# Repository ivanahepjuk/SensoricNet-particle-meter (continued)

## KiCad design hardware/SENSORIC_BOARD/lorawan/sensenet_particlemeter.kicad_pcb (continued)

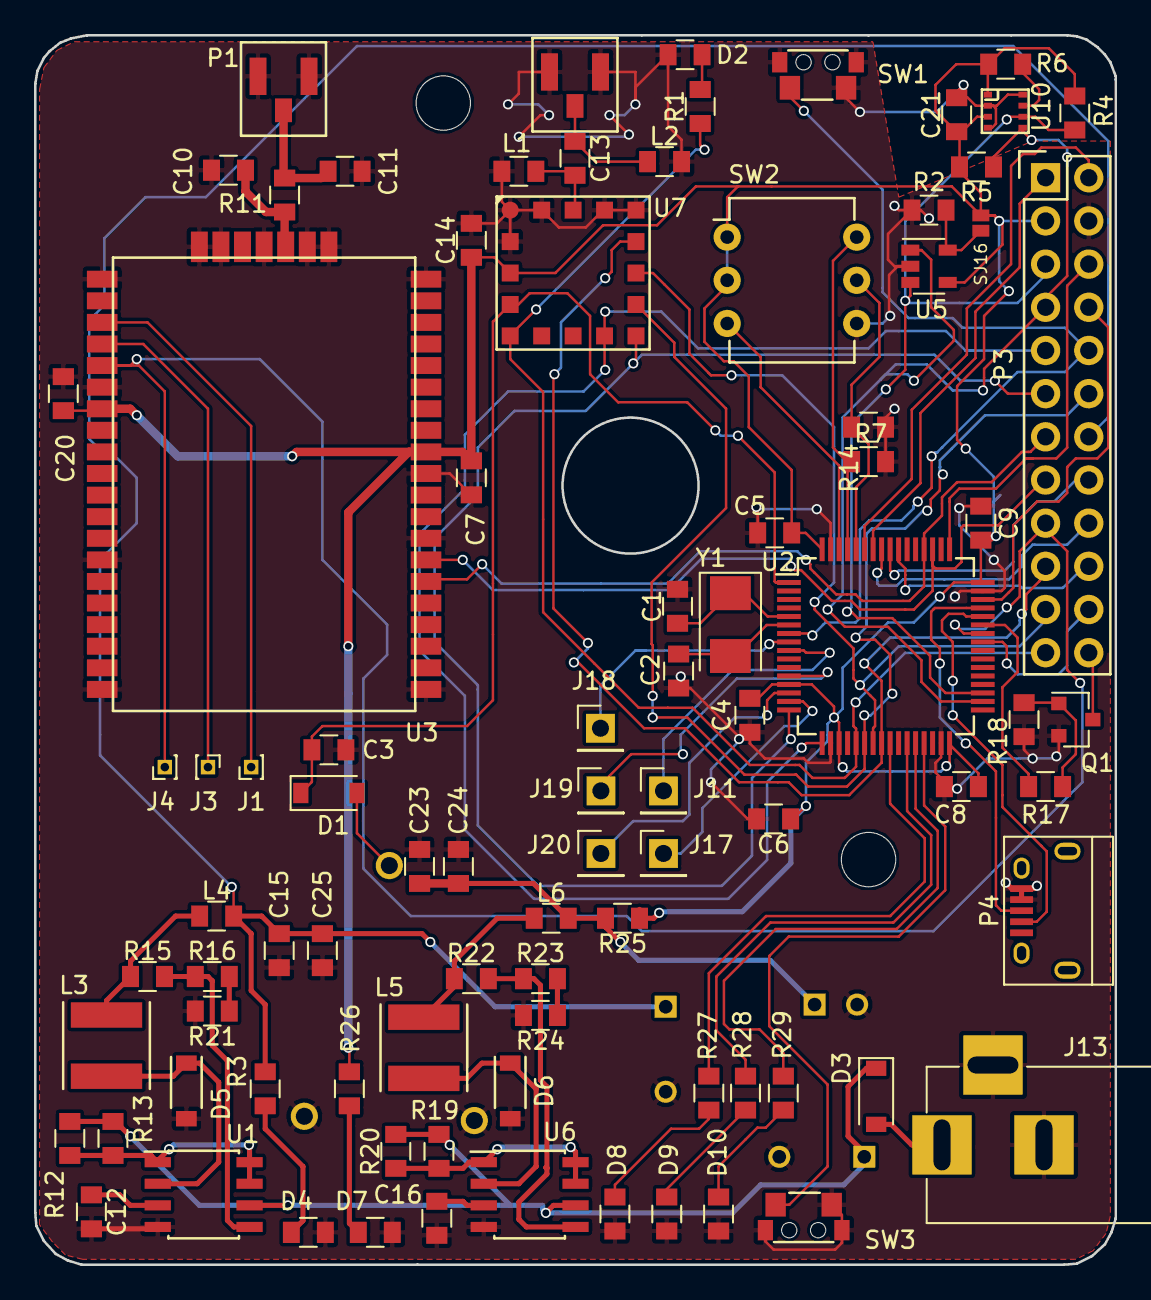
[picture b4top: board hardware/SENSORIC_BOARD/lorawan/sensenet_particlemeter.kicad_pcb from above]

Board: 2 copper layers, 63.6 x 72.3 mm, 95 parts (0 on the bottom side), 73 nets.

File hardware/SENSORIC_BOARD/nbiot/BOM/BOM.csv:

"Id";"Designator";"Package";"Quantity";"Designation";"Supplier and ref";
1;"U2";"TQFP-64_10x10mm_Pitch0.5mm";1;"stm32f072";;;
2;"BT1";"BAT-CR2032_bottom";1;"Battery_Cell";;;
3;"C3,C6,C9,C13,C4,C8";"SMD_0805";6;"C";;;
4;"C5,C7,C21,C25";"SMD_0805";4;"100n";;;
5;"C10,C11";"SMD_0805";2;"NC";;;
6;"C14";"SMD_0805";1;"2,2u";;;
7;"C23";"SMD_0805";1;"10u";;;
8;"C24";"SMD_0805";1;"220n";;;
9;"D1";"D_SOD-123";1;"D_Schottky";;;
10;"D2,D4,D7,D8,D9,D10";"SMD_0805";6;"LED";;;
11;"D3";"D_SOD-123";1;"D_Schottky_ss14";;;
12;"J1,J2,J3,J4,J21";"Pin_Header_Straight_1x01_Pitch1.00mm";5;"CONN_01X01";;;
13;"J5,J6";"MountingHole_3.2mm_M3_DIN965";2;"CONN_01X01";;;
14;"J13";"BARREL_JACK";1;"BARREL_JACK";;;
15;"L2,L1";"SMD_0805";2;"L";;;
16;"P1,P2";"Antenna_conn";2;"SMA_mini";;;
17;"R1,R17,R18,R27,R28,R29";"SMD_0805";6;"R";;;
18;"R2,R4,R5";"SMD_0805";3;"4.7k";;;
19;"R3,R26";"SMD_0805";2;"5k6";;;
20;"R6";"SMD_0805";1;"22k";;;
21;"R7,R10,R14";"SMD_0805";3;"10k";;;
22;"R8,R9";"SMD_0805";2;"1k";;;
23;"U3";"quectel_BC95";1;"QUECTEL_BC95";;;
24;"U7";"M10578";1;"M10578-A2";;;
25;"U10";"BME280";1;"bme280_barebone";;;
26;"J11,J17,J18,J19,J20";"Pin_Header_Straight_1x01_Pitch2.54mm";5;"CONN_01X01";;;
27;"SJ16";"solder_jumper";1;"solder_jumper";;;
28;"Y1";"Crystal_SMD_5032-2pin_5.0x3.2mm";1;"8MHz";;;
29;"C1,C2";"SMD_0805";2;"4.3p";;;
30;"C12";"SMD_0805";1;"510pF";;;
31;"C15";"SMD_0805";1;"1u";;;
32;"R12,R19";"SMD_0805";2;"0R33";;;
33;"R13,R20,R21,R24";"SMD_0805";4;"tbd";;;
34;"R15";"SMD_0805";1;"27k";;;
35;"R16";"SMD_0805";1;"9.1k";;;
36;"U1,U6";"SOIC-8_3.9x4.9mm_Pitch1.27mm";2;"MC33063";;;
37;"U5";"SOT-23-5";1;"CAT24C02";;;
38;"Q1";"SOT-23";1;"Q_NMOS_GSD";;;
39;"U4";"nanosimmm";1;"SIM";;;
40;"R11";"SMD_0805";1;"0R";;;
41;"C16";"SMD_0805";1;"352pF";;;
42;"R22";"SMD_0805";1;"18k";;;
43;"R23";"SMD_0805";1;"11k";;;
44;"R25,R30";"SMD_0805";2;"0R1";;;
45;"L3";"Inductor_Taiyo-Yuden_NR-50xx";1;"39uH";;;
46;"L5";"Inductor_Taiyo-Yuden_NR-50xx";1;"41uH";;;
47;"D5,D6";"SOD-123";2;"1N5819";;;
48;"C17,C19";"C_Radial_D10_L16_P5_bottom";2;"1000u";;;
49;"C18";"C_Radial_D6.3_L11.2_P2.5_bottom";1;"470uF";;;
50;"P3";"Pin_Header_Straight_2x12";1;"CONN_02X12";;;
51;"SW2";"DIP-6_W7.62mm";1;"SW_DIP_x03";;;
52;"SW1,SW3";"edge_switch";2;"SW_DPST";;;
53;"U8";"USB_Micro-B";1;"usb_femalee";;;
54;"L4,L6";"SMD_0805";2;"1uH";;;
55;"";"drawing";1;"";;;

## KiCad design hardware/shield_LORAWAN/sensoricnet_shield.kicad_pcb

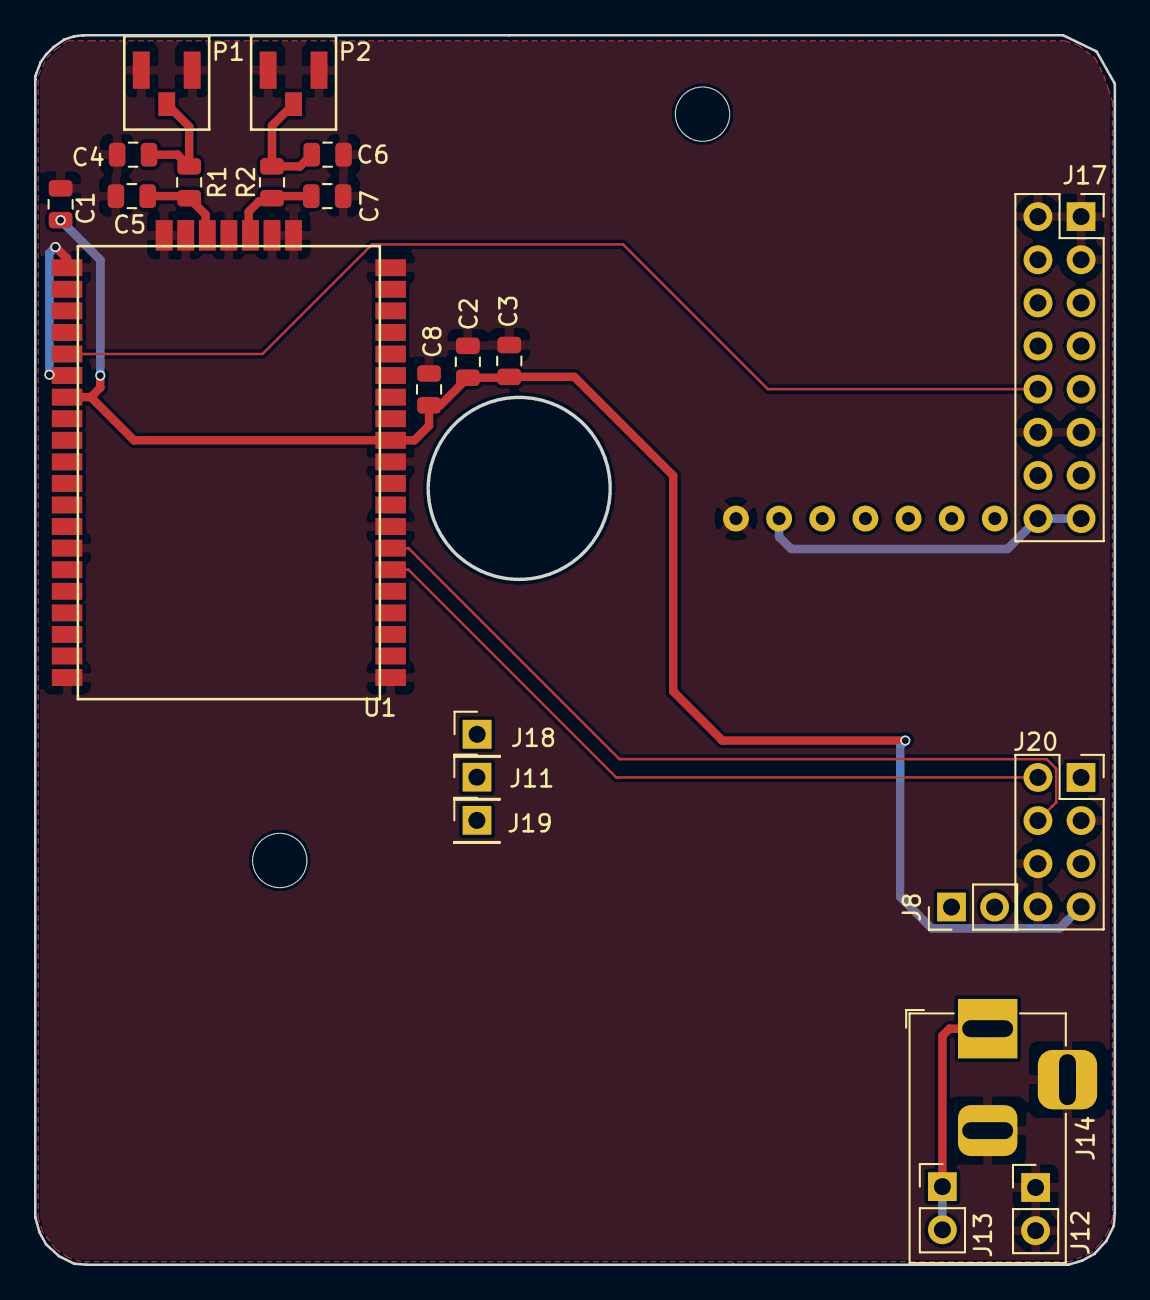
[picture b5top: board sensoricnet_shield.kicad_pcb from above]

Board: 2 copper layers, 63.6 x 72.4 mm, 27 parts (0 on the bottom side), 11 nets.

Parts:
C1, C8: 100n; C_0805_2012Metric
C2: 1u; C_0805_2012Metric
C3: 22p; C_0805_2012Metric
C4, C5, C6, C7: DNP; C_0805_2012Metric
J5, J6: CONN_01X01; MountingHole_3.2mm_M3_DIN965
J7: Conn_01x07_Female; OLED
J8: Conn_02x01; PinHeader_1x02_P2.54mm_Vertical
J11, J18, J19: CONN_01X01; PinHeader_1x01_P2.54mm_Vertical
J12: Barrel_Jack_Switch; BarrelJack_Horizontal
J13, J14: Conn_01x02_Female; PinHeader_1x02_P2.54mm_Vertical
J17: Conn_02x08_Odd_Even; PinSocket_2x08_P2.54mm_Vertical
J20: Conn_02x04_Odd_Even; PinSocket_2x04_P2.54mm_Vertical
LOGO1: LOGO; PCB_artwork
LOGO2: LOGO; OSHW-Logo2_9.8x8mm_BackSilkScreen
P1, P2: SMA_mini; Antenna_conn
R1, R2: 0R; R_0805_2012Metric
U1: RN2483; RN2483_top

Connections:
+3V3: C1.1, C2.1, C3.1, C8.2, J20.7, U1.12, U1.34
+5V: J7.2, J17.15, J17.16
+9V: J12.1, J13.1, J13.2
GND: C1.2, C2.2, C3.2, C4.1, C5.1, C6.1, C7.1, C8.1, J7.1, J12.2, J12.3, J14.1, J14.2, J17.1, J17.2, J17.3, J17.11, J17.12, J20.3, J20.6, J20.8, P1.1, P1.3, P2.1, P2.3, U1.1, U1.8, U1.11, U1.20, U1.21, U1.22, U1.24, U1.26, U1.27, U1.28, U1.33, U1.41, U1.47
unnamed: C4.2, P1.2, R1.1
unnamed: C5.2, R1.2, U1.25
unnamed: C6.2, P2.2, R2.1
unnamed: C7.2, R2.2, U1.23
Rx: J20.2, U1.6
Tx: J20.4, U1.7
WIRELESS_reset: J17.10, U1.32

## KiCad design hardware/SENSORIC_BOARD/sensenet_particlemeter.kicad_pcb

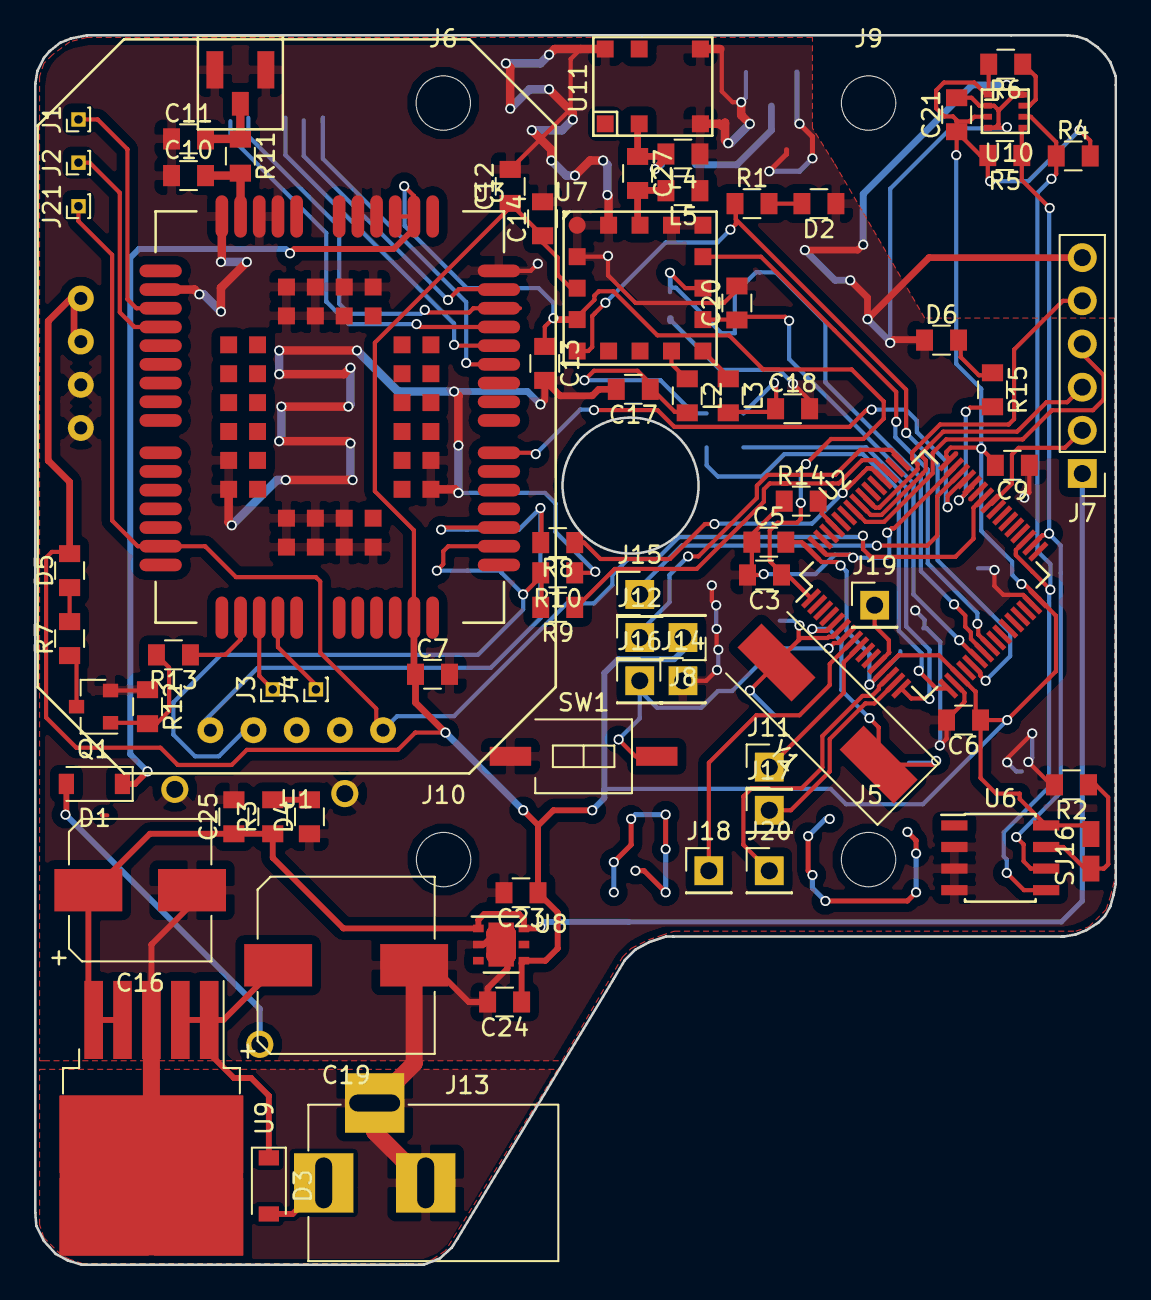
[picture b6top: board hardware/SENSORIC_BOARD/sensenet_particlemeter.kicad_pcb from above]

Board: 2 copper layers, 63.6 x 72.3 mm, 91 parts (0 on the bottom side), 64 nets.

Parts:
BT1: Battery_Cell; BAT-CR2032_bottom
C1, C2: 4.3p; SMD_0805_bottom
C3, C6, C9, C27: C; SMD_0805
C4, C8: C; SMD_0805_bottom
C5, C7, C21: 100n; SMD_0805
C10, C11: NC; SMD_0805
C12, C13, C17, C18, C20: 22p; SMD_0805
C14: 2,2u; SMD_0805
C16: 220n; CP_Elec_8x10
C19: 470u; CP_Elec_10x10
C22: 22p; SMD_0805_bottom
C23, C25: 10u; SMD_0805
C24: 220n; SMD_0805
D1: D_Schottky; D_SOD-123
D2, D4, D5, D6: LED; SMD_0805
D3: D_Schottky_ss14; D_SOD-123
J1, J2, J3, J4, J21: CONN_01X01; Pin_Header_Straight_1x01_Pitch1.00mm
J5, J6, J9, J10: CONN_01X01; MountingHole_3.2mm_M3_DIN965
J7: CONN_01X06; Pin_Header_Straight_1x06_Pitch2.54mm
J8, J11, J12, J14, J15, J16, J17, J18, J19, J20: CONN_01X01; Pin_Header_Straight_1x01_Pitch2.54mm
J13: BARREL_JACK
L2, L3: 47n; SMD_0805
L4, L5: L; SMD_0805
P1: SMA_mini; Antenna_conn
P2: SMA_mini; Antenna_conn_bott
Q1: Q_NPN_BCV71; SOT-23
R1: R; SMD_0805
R2, R4, R5, R13: 4.7k; SMD_0805
R3: 5k6; SMD_0805
R6: 22k; SMD_0805
R7, R8, R9, R15: 1k; SMD_0805
R10, R14: 10k; SMD_0805
R11: 0R; SMD_0805
R12: 47k; SMD_0805
SJ1, SJ15, SJ17: solder_jumper; solder_jumper_bott
SJ16: solder_jumper
SW1: SW_Push; SW_DIP_x1_W8.61mm_Slide_SMD_LowProfile
U1: wireless_patice; wireless_footprint
U2: stm32f072; TQFP-64_10x10mm_Pitch0.5mm
U3: QUECTEL_BC95; quectel_BC95
U4: SIM; nanosim_bottom
U6: M24C04; SOIC-8_3.9x4.9mm_Pitch1.27mm
U7: M10578-A2; M10578
U8: LD39050; DFN-6-1EP_3x3mm_Pitch0.95mm
U9: NCP59150; TO-263-5_TabPin3
U10: bme280_barebone; BME280
U11: SR4G008
Y1: 8MHz; Crystal_SMD_HC49-SD

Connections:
+3V3: C4.1, C5.2, C6.1, C7.1, C8.1, C9.2, C12.1, C14.1, C21.1, C23.1, C24.1, D5.2, J8.1, R4.2, R5.2, R6.2, SJ16.2, U1.1, U1.2, U2.13, U2.19, U2.32, U2.48, U2.64, U3.26, U6.8, U7.15, U8.4, U10.1, U10.3
+5V: C16.1, C25.1, J7.1, R3.1, U8.1, U8.6, U9.4, U9.5
GND: BT1.2, BT1.3, C1.2, C2.2, C3.2, C4.2, C5.1, C6.2, C7.2, C8.2, C9.1, C10.1, C11.1, C12.2, C13.2, C14.2, C16.2, C17.2, C18.2, C19.2, C20.2, C21.2, C22.2, C23.2, C24.2, C25.2, D2.1, D4.1, D6.1, J7.6, J13.2, J13.3, J14.1, L4.1, L5.1, P1.1, P1.3, P2.1, P2.3, Q1.2, R2.2, R10.1, R12.1, R14.1, SW1.1, U1.3, U1.4, U2.18, U2.31, U2.47, U2.63, U3.2, U3.43, U3.47, U3.48, U3.51, U3.52, U3.54, U3.59, U3.60, U3.61, U3.62, U3.63, U3.64, U3.65, U3.66, U3.71, U3.72, U3.73, U3.74, U3.81, U3.82, U3.83, U3.92, U3.93, U3.94, U6.2, U6.3, U6.4, U7.1, U7.2, U7.4, U7.5, U7.16, U8.2, U8.7, U9.3, U10.2, U10.4, U10.8, U11.3, U11.4, U11.6
unnamed: BT1.1, D1.2
unnamed: C1.1, U2.5, Y1.1
unnamed: C2.1, U2.6, Y1.2
unnamed: C10.2, R11.2, U3.53
unnamed: C11.2, P1.2, R11.1
unnamed: C17.1, L2.2, SJ15.2
unnamed: C18.1, L3.2, SJ17.2
unnamed: C19.1, D3.1, U9.1, U9.2
unnamed: C27.1, L4.2, SJ1.1, U11.2
unnamed: D2.2, R1.2
unnamed: D3.2, J13.1
unnamed: D4.2, R3.2
unnamed: D5.1, R7.2
unnamed: D6.2, R15.1
unnamed: J1.1, U3.3
unnamed: J2.1, U3.4
unnamed: J3.1, U3.19
unnamed: J4.1, U3.20
unnamed: J11.1, U2.9
unnamed: J17.1, U2.15
unnamed: J18.1, U2.8
unnamed: J19.1, U2.12
unnamed: J20.1, U2.14
unnamed: L2.1, U7.10
unnamed: L3.1, U7.9
unnamed: P2.2, SJ1.2
unnamed: Q1.1, R12.2, R13.2
unnamed: Q1.3, R7.1
unnamed: R2.1, SJ16.1, U6.7
unnamed: R6.1, U10.7
unnamed: R8.2, U1.5, U3.30
unnamed: R9.2, R10.2, U1.6, U3.29
unnamed: R13.1, U3.18
unnamed: R14.2, U2.60
unnamed: R15.2, U2.44
unnamed: U3.38, U4.6
unnamed: U3.39, U4.4
unnamed: U3.40, U4.1
unnamed: U3.41, U4.2
unnamed: U3.42, U4.5
PM_SCK: J7.5, U2.55
PM_SDI: J7.4, U2.57
PM_SDO: J7.3, U2.56
PM_SS: J7.2, U2.41
RI: U2.45, U3.34
Rx: R8.1, U2.52
SWD_CLK: J12.1, U2.49
SWD_DIO: J15.1, U2.46
Tx: R9.1, U2.51
UART_GPS_RX: SJ15.1, U2.17
UART_GPS_TX: SJ17.1, U2.16
WIRELESS_reset: J21.1, U1.9, U2.42, U3.15
antenna: C27.2, L5.2, U7.3
batt: C3.1, C13.1, D1.1, U2.1, U3.45, U3.46, U7.14
gps_fix: R1.1, U2.21, U7.13
gps_pulses: U2.24, U7.6
gps_reset: C22.1, U2.23, U7.7
gps_standby: C20.1, U2.22, U7.8
i2c_scl: R5.1, U2.34, U6.6, U10.5
i2c_sda: R4.1, U2.35, U6.5, U10.6
reset: J16.1, SW1.2, U2.7

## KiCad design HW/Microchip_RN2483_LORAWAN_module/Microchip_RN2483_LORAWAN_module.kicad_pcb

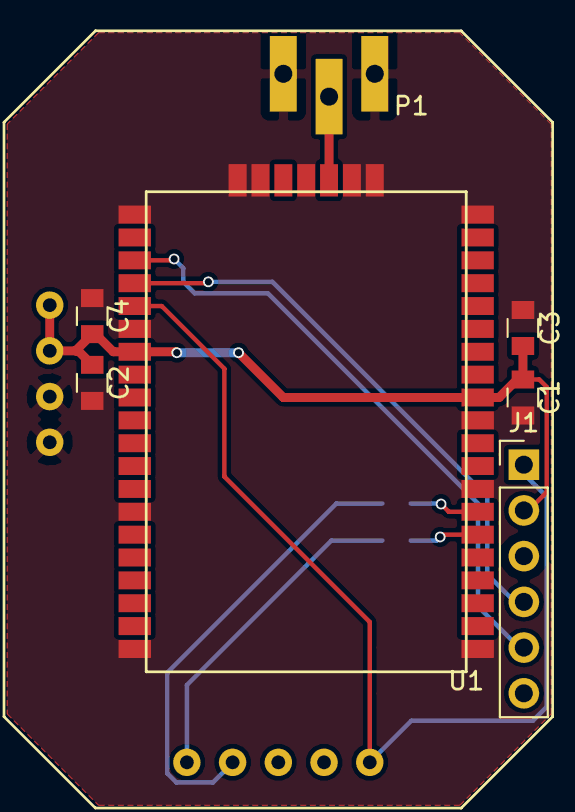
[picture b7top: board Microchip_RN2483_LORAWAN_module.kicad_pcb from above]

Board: 2 copper layers, 10 parts (0 on the bottom side), 10 nets.

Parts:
C1, C4: 100n; SMD_0805
C2, C3: 56p; SMD_0805
J1: Conn_01x06; Pin_Header_Straight_1x06_Pitch2.54mm
P1: SMA_mini; sma_conn
SJ1, SJ2: solder_jumper; solder_jumper_bott
U1: RN2483; RN2483_top
U2: wireless_patice; wireless_footprint

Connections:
+3V3: C1.1, C2.1, C3.2, C4.2, J1.2, U1.12, U1.34, U2.1, U2.2
GND: C1.2, C2.2, C3.1, C4.1, J1.3, P1.1, P1.3, U1.1, U1.8, U1.11, U1.20, U1.21, U1.22, U1.24, U1.26, U1.27, U1.28, U1.33, U1.41, U1.47, U2.3, U2.4
unnamed: J1.4, U1.31
unnamed: J1.5, U1.30
unnamed: P1.2, U1.23
unnamed: SJ1.1, U1.7
unnamed: SJ1.2, U2.6
unnamed: SJ2.1, U1.6
unnamed: SJ2.2, U2.5
rn2483_reset: J1.1, U1.32, U2.9

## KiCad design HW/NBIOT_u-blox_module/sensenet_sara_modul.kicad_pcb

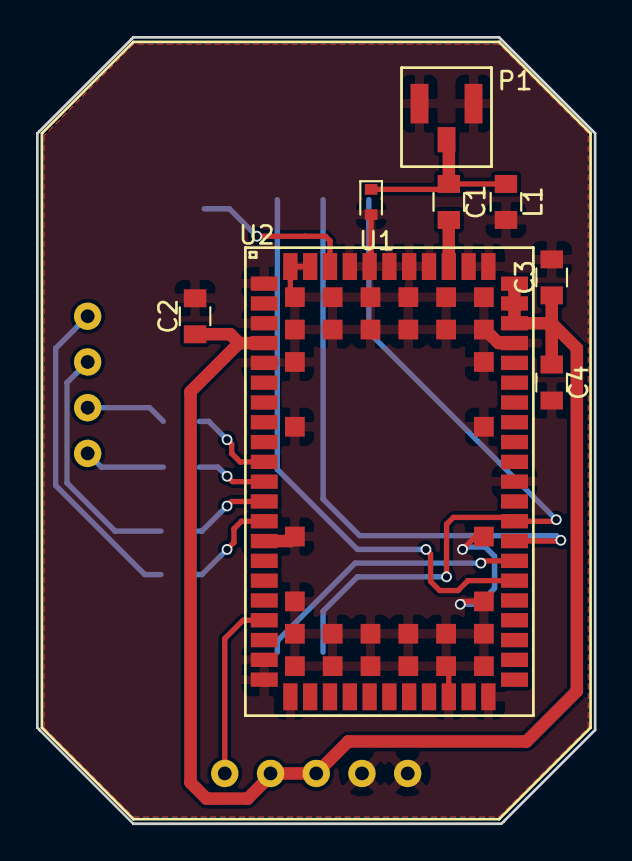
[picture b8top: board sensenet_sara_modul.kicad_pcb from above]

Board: 2 copper layers, 31.0 x 43.7 mm, 15 parts (0 on the bottom side), 18 nets.

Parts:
ANTENNA_DET1: ANTENNA_DET; smd_point_bottom
C1: 4.3pF; C_0805
C2, C4: 100n; C_0805
C3: 56p; C_0805
L1: L; C_0805
P1: SMA_mini; Antenna_conn
SJ1, SJ2, SJ3, SJ4: solder_jumper; solder_jumper_bott
U1: ESD5B5; D_SOD-523
U2: SARA-N210; SARA
U3: SIM; SIM2
U4: wireless_pcb_modul; wireless_footprint

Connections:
3.3V: C2.1, C3.1, C4.1, U2.4, U2.51, U2.52, U2.53, U4.6, U4.7
GND: C2.2, C3.2, C4.2, L1.2, P1.1, P1.3, U1.2, U2.1, U2.3, U2.5, U2.14, U2.20, U2.21, U2.22, U2.30, U2.32, U2.43, U2.50, U2.54, U2.55, U2.57, U2.58, U2.59, U2.60, U2.61, U2.63, U2.64, U2.65, U2.66, U2.67, U2.68, U2.69, U2.70, U2.71, U2.72, U2.73, U2.74, U2.75, U2.76, U2.77, U2.78, U2.79, U2.80, U2.81, U2.82, U2.83, U2.84, U2.85, U2.86, U2.87, U2.88, U2.89, U2.90, U2.91, U2.92, U2.93, U2.94, U2.95, U2.96, U3.3, U4.8, U4.9
unnamed: ANTENNA_DET1.1, U2.62
unnamed: C1.1, L1.1, P1.2, U1.1
unnamed: C1.2, U2.56
unnamed: SJ1.2, U2.11
unnamed: SJ2.2, U2.13
unnamed: SJ3.2, U2.10
unnamed: SJ4.2, U2.12
unnamed: U2.38, U3.6
unnamed: U2.39, U3.1
unnamed: U2.40, U3.5
unnamed: U2.41, U3.2, U3.4
SARA_reset: U2.18, U4.5
UART_CTS: SJ1.1, U4.4
UART_RTS: SJ3.1, U4.3
UART_RX: SJ2.1, U4.1
UART_TX: SJ4.1, U4.2

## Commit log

2018-01-02 This is the first official commit to the SensoricNet particle meter repository. In the past, there were more repositories and it was a bit chaotic, but from now there will be only one, both for fW an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
2018-01-02 picture added
2018-01-02 libopencm3 submodule tweaking eeej
2018-01-02 cleaning up a bit
2018-01-02 inc folder, src folder, makefile, cleaning
2018-01-02 bflmpsvz
2018-01-18 lorawan accepting commands
2018-01-22 opc-n2 improved booting stability
2018-01-27 a bit lost here
2018-01-29 hoooou hou hou
2018-01-31 mensi progres
2018-02-01 basic setup documentation for fedora
2018-02-05 spi problems
2018-02-05 spi stable, commit before cleaning
2018-02-06 SPI working, compilation errors cleaned, measured data are going out to USART4
2018-02-06 small update
2018-02-07 code refactorization
2018-02-07 folders juggling
2018-02-08 lorawan start
2018-02-14 predmdovolenou, dopiste co chcete, je to na vas..
2018-02-27 pridani cayenne lpp knihovny
2018-02-27 oprava gitignore
2018-03-04 cayennelpp, pokus o semihosting
2018-03-04 rozchozeni semihostingu, pridany debug vypisy
2018-03-04 encoding do hexa
2018-03-04 drobne opravy
2018-03-05 rozdelana prace na cteni dat z rn2483 po seriaku. nefunguje to ale
2018-03-06 pred tim nez to cele rozvrtam abych prisel na to kde je problem s opcn2
2018-03-06 ladime
2018-03-06 aaaa
2018-03-06 debug cteni z usartu, nefunguje to
2018-03-13 nejak se ztratilo readme...
2018-03-16 daily update - nefunguje usart4 receive chars
2018-03-17 z*urveny usart
2018-03-19 usart jede
2018-03-19 meri particles a odesila data
2018-03-21 memory leak asi opraveny
2018-03-21 Nb-IOT i LORAWAN ready na test stability, pridan main.h s konfiguracnima definama, uklizeno v ramci moznosti
2018-04-02 eeprom write dodelat
2018-04-03 Pripraveno na eeprom cteni/zapis ID
2018-04-03 priprava na gps modul
2018-04-04 cteni/psani do eeprom funguje
2018-04-06 AAAAAAAA nesnasim particle meter
2018-04-06 asi to jede a bude potreba vyresit robustnejsi zdroje
2018-04-11 uklid kodu, lora zase funkcni, pridan provisioning z csv souboru
2018-04-12 lora: oprava datarate, prubezne ukladani frame counteru
2018-04-13 pokus dale ucesat kod, ale nejak se mi to ted seka a nemam u sebe debug. tento commit nemergeovat!
2018-04-13 vypada to funkcne, z nejakeho duvodu musim odpojit programator
2018-04-15 pokus o uchozeni mereni relativni vlhkosti. zkontroloval jsem kompenzacni matematiku a nevidim tam problem, relativni vlhkost to uz meri, ale se zapornym znamenkem, coz zjevne neni ok. TODO
2018-04-16 upstream merge
2018-04-16 oprava cteni relativni vhlkosti a uklid v knihovne (volani zacinaji na BME_)
2018-04-18 wtf commit
2018-05-02 daily
2018-05-02 usart 4 na wireless mi funguje preruseni, tzn kdyz do patice od wireless pripojim ftdi externi adapter, tak cokoliv v terminalu napisu, snpm mi vrati zpet.
2018-05-02 interrupt predelany na USART2, ale neotestovany, protoze na vyvojove desce je USART2 pristupny po odpajeni jumperu
2018-05-12 pred gps branch
2018-05-13 gps ladeni, nbiot_connect() je zakomentovana
2018-05-13 download nove libopencm3, uprava makefile - doplneni jineho ld scriptu
2018-05-14 rozdelany histogram
2018-05-26 vikend gps pred
2018-05-26 testcommit
2018-05-26 gps fixuje, interrupt jede
2018-05-27 posila hromady znaku a v preruseni precte data z gps
2018-05-28 nejak se to rozbilo, checkout zpatky
2018-05-29 vytahne z gpsky floaty souradnic
2018-06-08 ani nevim, co sem timto myslel
2018-07-13 nbiot preroutovany
2018-07-13 nbiot preroutovany 2
2018-07-14 Zaklad nove verze je hotovy, ted jdu udelat vetsi zmeny v napajeni a layoutu, priprava na shield atd.
2018-07-14 Novy rozmer desky, zmena napajeni z LDO na step down, pridany 1000uF na 5V
2018-07-17 zonglovani zase s gitem
2018-07-18 objednavam prototypy
2018-07-19 pridana kompilace gps souradnic. workaround nefunkcni gps
2018-07-19 Revert "pridana kompilace gps souradnic. workaround nefunkcni gps"
    This reverts commit 8a733ff54c9069909556b1e6c9c11308b894000c.
2018-07-19 pridana kompilace gps souradnic z csv jako workaround nefunkcni gps
2018-07-30 pred debugem noveho hardwaru
2018-08-04 modifikace led diod v hw verzi 2
2018-08-08 redefinice led, inicializace USART1 pro debug vystupy, debug fce
2018-08-13 cteni z gps funkcni, parsovani priste...
2018-08-14 v get_nth_substring je chyba, ale radeji to commitnu a odladim potom
2018-08-15 neotestovana oprava
2018-08-15 naznak parsingu gps pozice
2018-08-16 dodelano parsovani gps souradnic, bez anteny to bohuzel neoverim
2018-08-18 nadhozeny konvert gps to wgs, todo
2018-08-19 funkce pro konverzi gps na wgs84, je to kompilovatelne, nutne otestovat
2018-08-19 opravy a testovani
2018-08-28 funkcni cteni z gps a odesilani souradnic pres IoT
2018-09-04 blabla
2018-09-05 pokus o opravu prepoctu formatu gps souradnic. Nemam jak otestovat
2018-09-05 rozchazeni
2018-09-05 oprava velikosti gps promennych a doplneni prepoctu E-W a N-S
2018-09-06 pred mergnutim opravy souradnic
2018-09-06 Startovaci bod pro praci na hw 2.0
2018-09-07 pred zonglovanim s githubem
2018-09-07 libopencm3 problems
2018-09-07 snad sem vyhodil libopencm3 z tracked files..?
2018-09-07 Cteni statistik site
2018-09-07 Cteni statistik site 2
2018-09-07 poresene preruseni pri cteni z SPI
2018-09-07 opravene zamrzani kvuli preruseni - tedka je preruseni na gpsce aktivni jen kdyz se ceka na konci smycky
2018-09-19 pred prepnuti do nove vetve
2018-09-24 pred displayem
2018-10-16 novy hw
2018-10-17 oled nejede
2018-10-18 pm divnej
2018-11-20 snazim se rozchodit novou serii, jebne me z toho z chvili
2018-11-21 novy hw FLASHABLE, watchdog resi spoustu problemu:)
2018-11-21 prvni deska trial run, NMOSem spinany pmeter
2018-11-24 watchdog restartuje, posila se statistika site, nektere padaji a nektere ne
2018-11-28 FW do Liberce
2018-11-28 5 sensoru flashnuto, stability check
2018-11-30 pridani reboot signau, opraveni pullupu u particlemeteru
2018-12-04 problemy s cpol cpha, pokus o stabilni fw
2018-12-04 PARTICLMETER GLITCH odstranen???
2018-12-05 posila casteji, pokus o odstraneni rebootu
2018-12-13 GOLDEN VERSION opravene warningy, wwatchdog, pojede pres vanoce?
2019-01-25 zonglovani s repama
2019-02-12 rozdelane upravicky
2019-02-13 dalsi updaty
2019-02-14 Daily update, rework zdroju - oba dva LDO s adjustem, 5Venable, pico clasp connector, priprava na lorawan shield
2019-02-15 daily, jeste musim prehodit gps doprava
2019-02-19 finalizing nbiot
2019-02-19 VELKY UKLID
2019-02-19 artwork, aligning, checking, polishing..
2019-02-20 SENSORICNET mother board v.: 1.0
2019-02-20 priprava FAB data
2019-02-20 readme v HW slozce, obrazky
2019-02-20 uklid zase
2019-02-22 uklid
2019-02-25 pokracuju
2019-02-25 shield template added
2019-02-25 LORAWAN shield 1.0 added
2019-03-07 verze 1.0 manufacture files
2019-03-07 verze 1.0 manufacture files + pictures, readme.MD
2019-03-07 verze 1.0 manufacture files + pictures, readme.MD tweaking
2019-05-05 gerbers added
2019-05-05 cleaning the code
2019-05-05 code cleaning, BETA VERSION
2019-05-21 bme280 on off added to main.h (by #define)
2019-07-09 lorawan gerbers
2019-07-09 last version on my hdd
2019-07-10 lorawan schematics added
